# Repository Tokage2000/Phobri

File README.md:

# Phobri
Repository for a modification of the Phob motherboard to fit an Hori Pad GCC

Potential issues: <br />

LR pads are a bit too small, you may need to glue them/stick them in place if you plan to use them. <br />

You have to cut the inner top of the shell and the start button. <br />
 <br />

Cstick may be awkward to connect. <br />
 <br />

Phob repositories: https://github.com/PhobGCC

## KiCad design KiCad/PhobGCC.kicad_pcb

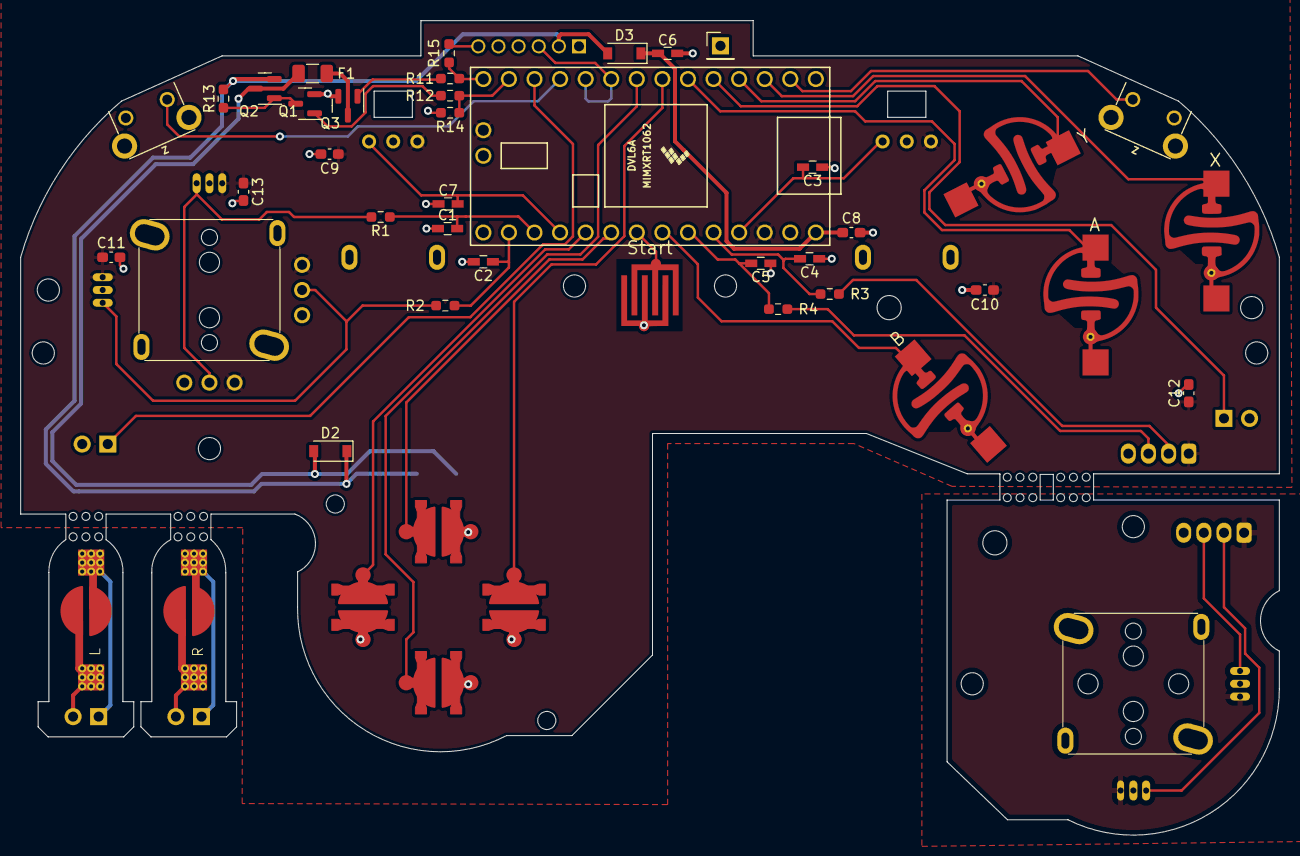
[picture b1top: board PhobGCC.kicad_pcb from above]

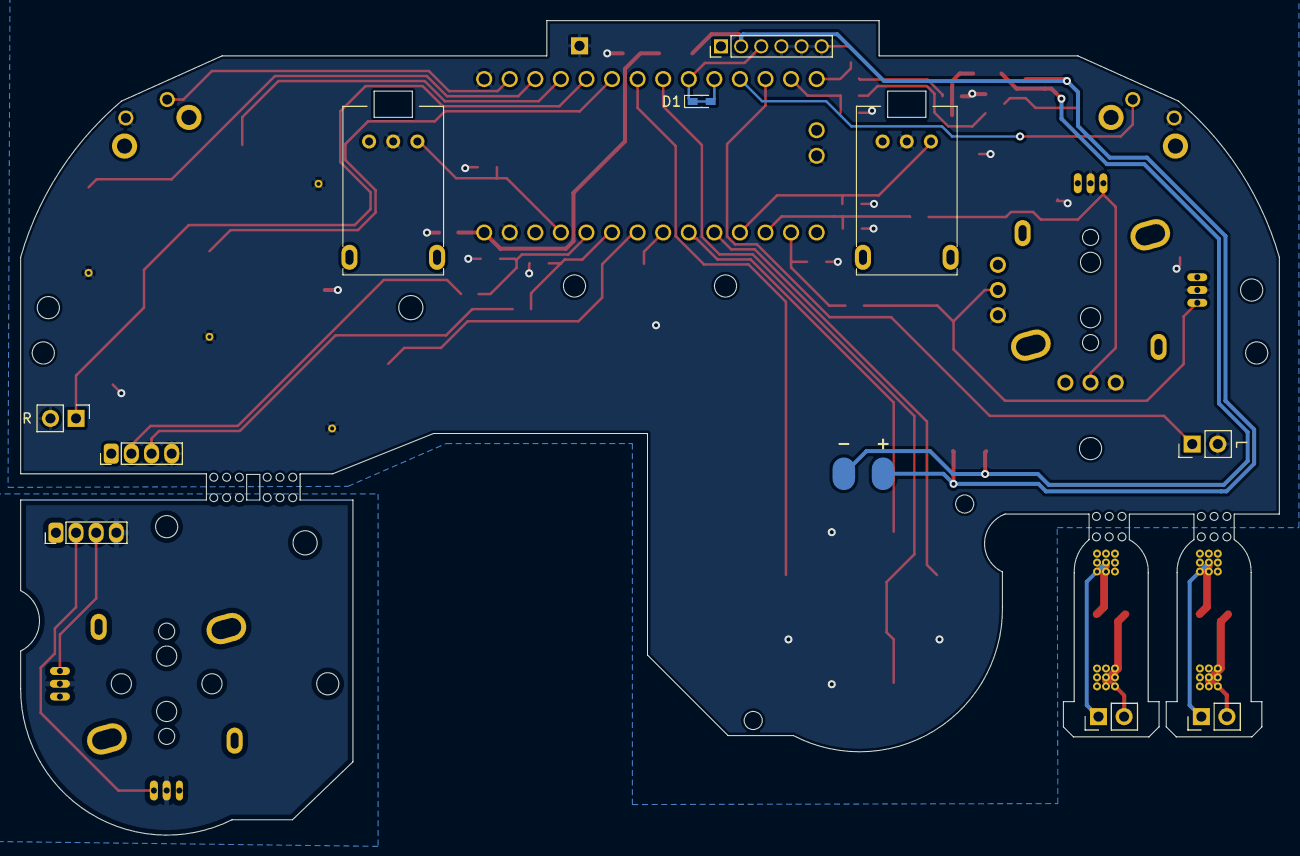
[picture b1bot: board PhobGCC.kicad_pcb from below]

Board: 2 copper layers, 125.0 x 80.9 mm, 75 parts (13 on the bottom side), 41 nets.

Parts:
C1, C2, C3, C4, C5, C7: 0.047u; C_0603_HandSoldering
C6: 10u; C_0603_HandSoldering
C8, C9, C10, C11, C12, C13: 1u; C_0603_1608Metric_Pad1.08x0.95mm_HandSolder
D1: D_Schottky_Shorted; D_SOD-523_Shorted
D2, D3: M7C; D_SOD-123
F1: Fuse; Fuse_1206_3216Metric
H7, H7#2: 2.4mm; MountingHole_2.4mm
H8, H8#2, H8#3, H8#4, H8#5, H8#6, H8#7, H8#8, H8#9: 2.2mm; MountingHole_2.2mm
H10, H10#2: MountingHole; MountingHole_1.8mm
H12, H13: MountingHole; MountingHole_2.0mm
H14, H15: MouseBite; breakaway-mousebites-double
H16: MouseBiteLA; breakaway-mousebites-double
H17: MouseBiteRA; breakaway-mousebites-double
J1: Conn_01x06_Female; GCC_Header_Straight_1x06_Pitch2.00mm
J2: Conn_01x04_Female; PinHeader_1x04_P2.00mm_Vertical
J3: Conn_01x01_Male; PinHeader_1x01_P2.54mm_Vertical
J4: Conn_01x04_Male; PinHeader_1x04_P2.00mm_Vertical
J5: Rumble; rumble_pins
J6: L; Pin_Header_Straight_1x02_Pitch2.54mm
J7: R; Pin_Header_Straight_1x02_Pitch2.54mm
Q1, Q3: Q_NMOS_GSD; SOT-23
Q2: Q_PMOS_GDS; SOT-23
R1, R2, R3, R4: 2k; R_0603_1608Metric_Pad0.98x0.95mm_HandSolder
R11, R12: 100R; R_0603_1608Metric_Pad0.98x0.95mm_HandSolder
R13, R14, R15: 10k; R_0603_1608Metric_Pad0.98x0.95mm_HandSolder
RV1, RV2: R_POT_MountingPin; GCC_Slider
SW1: A; ABXY_Contact_Omron_Switch
SW2: B; ABXY_Contact_Omron_Switch
SW3: X; ABXY_Contact_Omron_Switch
SW4: Y; ABXY_Contact_Omron_Switch
SW5: Start; Start_Contact
SW6: L; Pin_Header_Straight_1x02_Pitch2.54mm
SW7: R; Pin_Header_Straight_1x02_Pitch2.54mm
SW8, SW8#2: Z; Z_Switch_Edge_Omron
SW9: Dleft; Dpad_Contact_TL3315NF_2
SW10: Dup; Dpad_Contact_TL3315NF_2
SW11: Dright; Dpad_Contact_TL3315NF_2
SW12: Ddown; Dpad_Contact_TL3315NF_2
SW13: L; Trigger_Contact
SW14: R; Trigger_Contact
U1: Teensy4.0; Teensy40_Edge_Pins
U2: 2x DRV5053CAQLPGM Hall Effect Sensors; GCC_Stickbox_2
U5: Stickbox_Assembly; GCC_Stickbox_Hall_Only

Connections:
+3V3: C9.1, C10.1, C11.1, C12.1, C13.1, J2.1, RV1.1 (V+), RV2.1 (V+), U1.16 (3V3), U1.31 (3V3), U2.1 (H1XV), U2.4 (H1YV), U2.15 (P1XV), U2.18 (P1YV)
+5V: D2.1 (K), D3.2 (A), J1.2, J5.1, Q2.2 (S), R13.2
/A: SW1.1, U1.6 (4_BCLK2)
/B: SW2.1, U1.27 (20_A6_TX5_LRCLK1)
/Brake: R12.1, R14.2, U1.13 (11_MOSI_CTX1)
/C_x: J2.2, R3.2
/C_x_filt: C4.1, R3.1, U1.29 (22_A8_CTX1)
/C_y: J2.3, R4.2
/C_y_filt: C5.1, R4.1, U1.28 (21_A7_RX5_BCLK1)
/Data: D1.1 (K), D1.2 (A), J1.3, U1.9 (7_RX2_OUT1A), U1.10 (8_TX2_IN1)
/Ddown: SW12.1, U1.8 (6_OUT1D)
/Dleft: SW9.1, U1.24 (17_A3_TX4_SDA1)
/Dright: SW11.1, U1.7 (5_IN2)
/Dup: SW10.1, U1.25 (18_A4_SDA0)
/L: SW6.1, U1.12 (10_CS_MQSR)
/Lanalog: C7.1, RV1.3 (Signal), U1.23 (16_A2_RX4_SCL1)
/R: SW7.1, U1.5 (3_LRCLK2)
/Ranalog: C3.1, RV2.3 (Signal), U1.30 (23_A9_CRX1_MCLK1)
/Rumble: R11.1, R15.2, U1.14 (12_MISO_MQSL)
/Start: SW5.1, U1.26 (19_A5_SCL0)
/Stick_x: R1.2, U2.3 (H1XS), U2.14 (P1XS)
/Stick_x_filt: C1.1, R1.1, U1.22 (15_A1_RX3_SPDIF_IN)
/Stick_y: R2.2, U2.6 (H1YS), U2.17 (P1YS)
/Stick_y_filt: C2.1, R2.1, U1.21 (14_A0_TX3_SPDIF_OUT)
/X: SW3.1, U1.3 (1_TX1_CTX2_MISO1)
/Y: SW4.1, U1.4 (2_OUT2)
/Z: SW8#2.1, U1.2 (0_RX1_CRX2_CS1)
GND: C1.2, C2.2, C3.2, C4.2, C5.2, C6.2, C7.2, C8.2, C9.2, C10.2, C11.2, C12.2, C13.2, J1.4, J1.5, J1.6, J2.4, J3.1, J4.4, Q1.2 (S), Q3.2 (S), R14.1, R15.1, RV1.2 (GND), RV2.2 (GND), SW1.2, SW2.2, SW3.2, SW4.2, SW5.2, SW6.2, SW7.2, SW8.1, SW8#2.2, SW9.2, SW10.2, SW11.2, SW12.2, U1.1 (GND), U1.17 (GND), U1.32 (GND), U2.2 (H1XG), U2.5 (H1YG), U2.13 (P1XG), U2.16 (P1YG), U5.2 (H1XG), U5.5 (H1YG)
unnamed: C6.1, C8.1, D3.1 (K), U1.33 (VIN)
unnamed: D2.2 (A), F1.1, J5.2, Q2.3 (D)
unnamed: F1.2, Q3.3 (D)
unnamed: J4.2, U5.3 (H1XS)
unnamed: J4.3, U5.6 (H1YS)
unnamed: J6.1, SW13.1
unnamed: J6.2, SW13.2
unnamed: J7.1, SW14.1
unnamed: J7.2, SW14.2
unnamed: Q1.1 (G), R12.2
unnamed: Q1.3 (D), Q2.1 (G), R13.1
unnamed: Q3.1 (G), R11.2
VCC: J4.1, U5.1 (H1XV), U5.4 (H1YV)

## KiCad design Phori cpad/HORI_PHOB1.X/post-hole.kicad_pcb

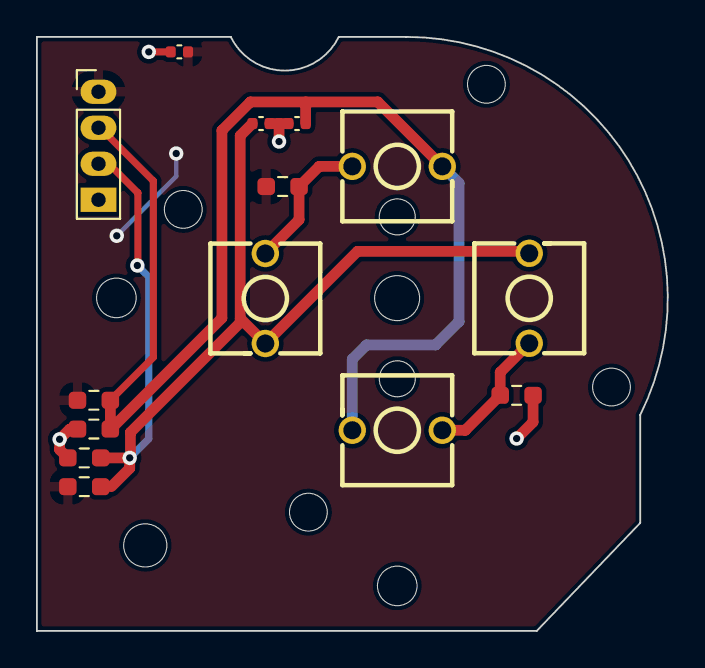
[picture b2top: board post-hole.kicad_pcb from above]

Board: 2 copper layers, 35.0 x 33.0 mm, 24 parts (0 on the bottom side), 6 nets.

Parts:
C1, C2, C3: 100n; C_0402_1005Metric
H1, H2, H3, H4: MountingHole; MountingHole_2.1mm
H5: MountingHole; MountingHole_2.5mm
H7: 2.4mm; MountingHole_2.4mm
H8, H8#2: 2.2mm; MountingHole_2.2mm
H12, H12#2: MountingHole; MountingHole_2.0mm
J1: Conn_01x04; PinHeader_1x04_P2.00mm_Vertical
R1, R2: 1.1k; R_0603_1608Metric_Pad0.98x0.95mm_HandSolder
R5, R6, R7, R8: 5.6k; R_0603_1608Metric_Pad0.98x0.95mm_HandSolder
SW1: C_left; SW-TH_L6.2-W6.2-P5.00
SW2: C_up; SW-TH_L6.2-W6.2-P5.00
SW3: C_down; SW-TH_L6.2-W6.2-P5.00
SW4: C_right; SW-TH_L6.2-W6.2-P5.00

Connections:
/C_x: C3.1, J1.2, R7.2, R8.1, SW1.2, SW4.2
/C_y: C2.1, J1.3, R5.2, R6.1, SW2.2, SW3.2
GND: C1.2, C2.2, C3.2, J1.4, R1.2, R6.2, R8.2
unnamed: R1.1, SW1.1, SW3.1
unnamed: R2.1, SW2.1, SW4.1
VCC: C1.1, J1.1, R2.2, R5.1, R7.1

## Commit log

2022-07-20 Version 1
2022-07-20 Update README.md
    Added a list of currently known issues or potential issues
2022-08-10 Upate to readme post build
2022-08-29 Added a mod of the 0.24 Phob SW with the Hori Z button set to Z
2022-10-24 Added modified 0.27 SW with 2nd Z set to copy Z
2023-02-22 added sw version 0.28
2023-05-25 added sw version 0.29
2023-08-08 added the hori cpad files
